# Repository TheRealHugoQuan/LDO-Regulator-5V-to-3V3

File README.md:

# ⚡ 5V to 3.3V LDO Regulator Board

## 📖 Overview
This repository contains the hardware design files for a custom Low Dropout (LDO) linear voltage regulator PCB. The board is designed to step down a standard 5V input supply to a stable, clean 3.3V output, making it ideal for powering sensitive 3.3V microcontrollers, sensors, and communication modules.

The PCB was designed from scratch using **KiCad**.

## 🛠️ Hardware Specifications
* **Input Voltage (Vin):** 5.0V (Standard USB or generic 5V rail)
* **Output Voltage (Vout):** 3.3V
* **Maximum Output Current:** [e.g., 500mA / 1A]
* **LDO Component:** [e.g., AMS1117-3.3, AP2112K-3.3]
* **Capacitors:** Includes required input and output decoupling capacitors ([e.g., 10uF Ceramic]) for transient stability and noise reduction.
* **Dimensions:** [e.g., 15mm x 20mm]
* **Layers:** 2-Layer FR4

## 📐 Schematic & Board Layout
*(Optional but highly recommended: Take a screenshot of your schematic and your 3D KiCad viewer, save them in an `images` folder in this repo, and uncomment the lines below to display them!)*

## 📁 Repository Structure
* `/` - Root directory containing the core KiCad project files (`.kicad_pro`, `.kicad_sch`, `.kicad_pcb`).
* `/[Manufacturing or Gerbers Folder]/` - Exported Gerber files and drill files ready for PCB fabrication (JLCPCB, PCBWay, etc.).
* `/3DModel/` - 3D step files for specific components (if applicable).

## 🚀 Getting Started
To view or modify this design:
1. Install [KiCad](https://www.kicad.org/) (Version 7.0 or newer recommended).
2. Clone this repository to your local machine:
   ```bash
   git clone

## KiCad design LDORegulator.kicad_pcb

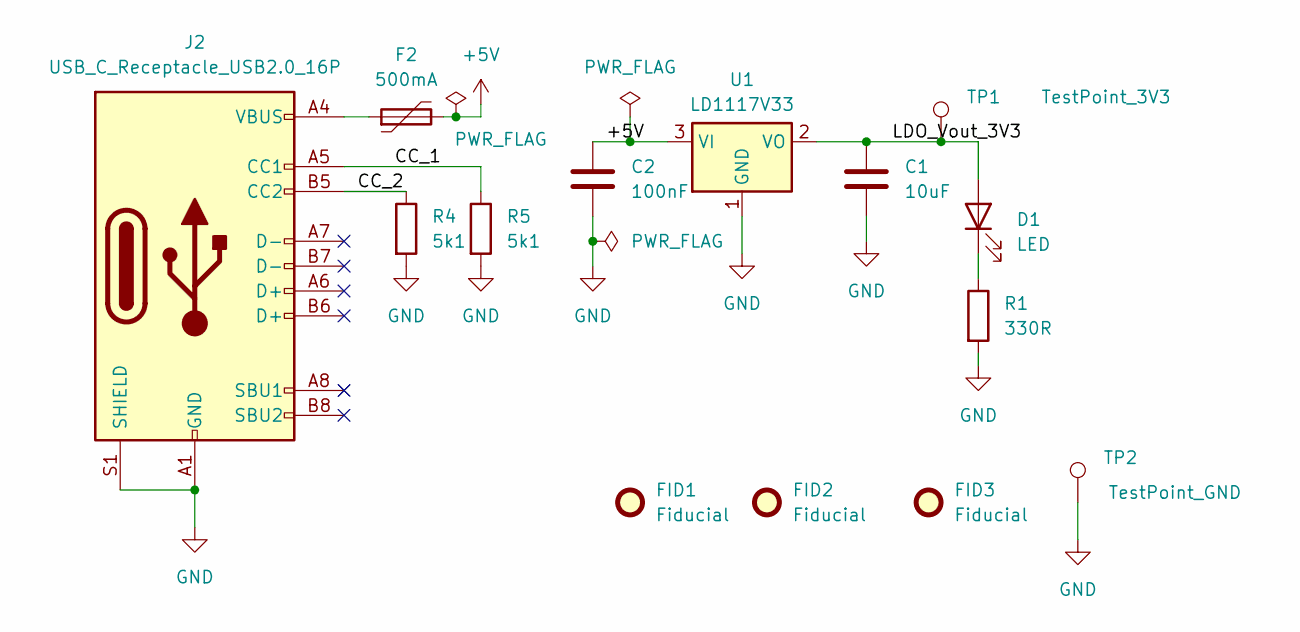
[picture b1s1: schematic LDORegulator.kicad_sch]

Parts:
C1: 10uF; C_0603_1608Metric; Manufactuer Part No. CL10A106MQ8NNNC
C2: 100nF; C_0402_1005Metric; Manufactuer Part No. CL05B104KO5NNNC
D1: LED; LED_0603_1608Metric; Manufactuer Part No. 19-217/G7C-AL1M2B/3T
F2: 500mA; Fuse_1206_3216Metric; Manufactuer Part No. nSMD050-13.2V
FID1, FID2, FID3: Fiducial; Fiducial_1mm_Mask2mm
J2: USB_C_Receptacle_USB2.0_16P; USB_C_Receptacle_HRO_TYPE-C-31-M-12
R1: 330R; R_0402_1005Metric; Manufactuer Part No. 0603WAF3300T5E
R4, R5: 5k1; R_0603_1608Metric; Manufactuer Part No. 0603WAF5101T5E
TP1: TestPoint_3V3; TestPoint_Pad_1.5x1.5mm
TP2: TestPoint_GND; TestPoint_Pad_1.5x1.5mm
U1: LD1117V33; SOT-223-3_TabPin2; Manufactuer Part No. AMS1117-3.3

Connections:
+5V: C2.1, F2.2, U1.3 (VI)
/CC_1: J2.A5 (CC1), R5.1
/CC_2: J2.B5 (CC2), R4.1
/LDO_Vout_3V3: C1.1, D1.2 (A), TP1.1, U1.2 (VO)
GND: C1.2, C2.2, J2.A1 (GND), J2.A12 (GND), J2.B1 (GND), J2.B12 (GND), J2.S1 (SHIELD), R1.2, R4.2, R5.2, TP2.1, U1.1 (GND)
unnamed: D1.1 (K), R1.1
unnamed: F2.1, J2.A4 (VBUS), J2.A9 (VBUS), J2.B4 (VBUS), J2.B9 (VBUS)

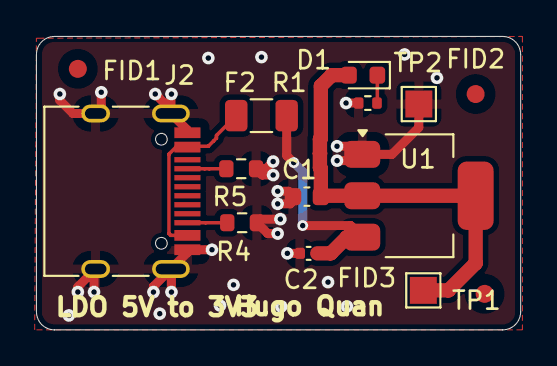
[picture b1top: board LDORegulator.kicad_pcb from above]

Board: 2 copper layers, 26.9 x 16.3 mm, 14 parts (0 on the bottom side), 7 nets.

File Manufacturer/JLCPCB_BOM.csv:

Comment,Designator,Footprint,JLCPCB Part # (optional)
10uF,C1,Capacitor_SMD:C_0603_1608Metric,C19702
100nF,C2,Capacitor_SMD:C_0402_1005Metric,C1525
LED,D1,LED_SMD:LED_0603_1608Metric,C72043
500mA,F2,Fuse:Fuse_1206_3216Metric,C83921
USB_C_Receptacle_USB2.0_16P,J2,Connector_USB:USB_C_Receptacle_HRO_TYPE-C-31-M-12,
330R,R1,Resistor_SMD:R_0402_1005Metric,C23138
5k1,"R4,R5",Resistor_SMD:R_0603_1608Metric,C23186
TestPoint_3V3,TP1,TestPoint:TestPoint_Pad_1.5x1.5mm,
TestPoint_GND,TP2,TestPoint:TestPoint_Pad_1.5x1.5mm,
LD1117V33,U1,Package_TO_SOT_SMD:SOT-223-3_TabPin2,C6186

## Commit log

2026-03-08 new file
2026-03-08 Create README for LDO Regulator Board project
    Add README with project overview and specifications
